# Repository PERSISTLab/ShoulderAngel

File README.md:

# Shoulder Angel: An Open Platform for Reprogramming Wayward Wireless Sensors

Software bugs are a critical threat to the deployability and maintainability of low-power wireless sensors, resulting in excess power consumption, hardware misconfigurations, incorrect data, and shortened device lifetimes. Worse, these errors can prevent wireless reprogramming, resulting in longer delays and costly human interventions. This repository contains the  Shoulder Angel—an ultra-low-power, low-cost, open hardware and software platform that ensures users can always recover and reprogram wireless sensors, in spite of software errors. Shoulder Angel uses a physically separate coprocessor to monitor a device’s power consumption and other behaviors, while keeping the device in a reprogrammable state. Our results show that Shoulder Angel is able to recover from otherwise fatal software errors while incurring an energy overhead of only 7 μW.

### Getting Started
Coming soon....

### License

```
Copyright (c) 2016 PERSIST Lab

Permission is hereby granted, free of charge, to any person obtaining a copy of this software 
and associated documentation files (the "Software"), to deal in the Software without restriction, 
including without limitation the rights to use, copy, modify, merge, publish, distribute, sublicense,
and/or sell copies of the Software, and to permit persons to whom the Software is furnished to do 
so, subject to the following conditions:

The above copyright notice and this permission notice shall be included in all copies or substantial
portions of the Software.

THE SOFTWARE IS PROVIDED "AS IS", WITHOUT WARRANTY OF ANY KIND, EXPRESS OR IMPLIED, 
INCLUDING BUT NOT LIMITED TO THE WARRANTIES OF MERCHANTABILITY, FITNESS FOR A PARTICULAR
PURPOSE AND NONINFRINGEMENT. IN NO EVENT SHALL THE AUTHORS OR COPYRIGHT HOLDERS BE LIABLE
FOR ANY CLAIM, DAMAGES OR OTHER LIABILITY, WHETHER IN AN ACTION OF CONTRACT, TORT OR 
OTHERWISE, ARISING FROM, OUT OF OR IN CONNECTION WITH THE SOFTWARE OR THE USE OR OTHER 
DEALINGS IN THE SOFTWARE.
```

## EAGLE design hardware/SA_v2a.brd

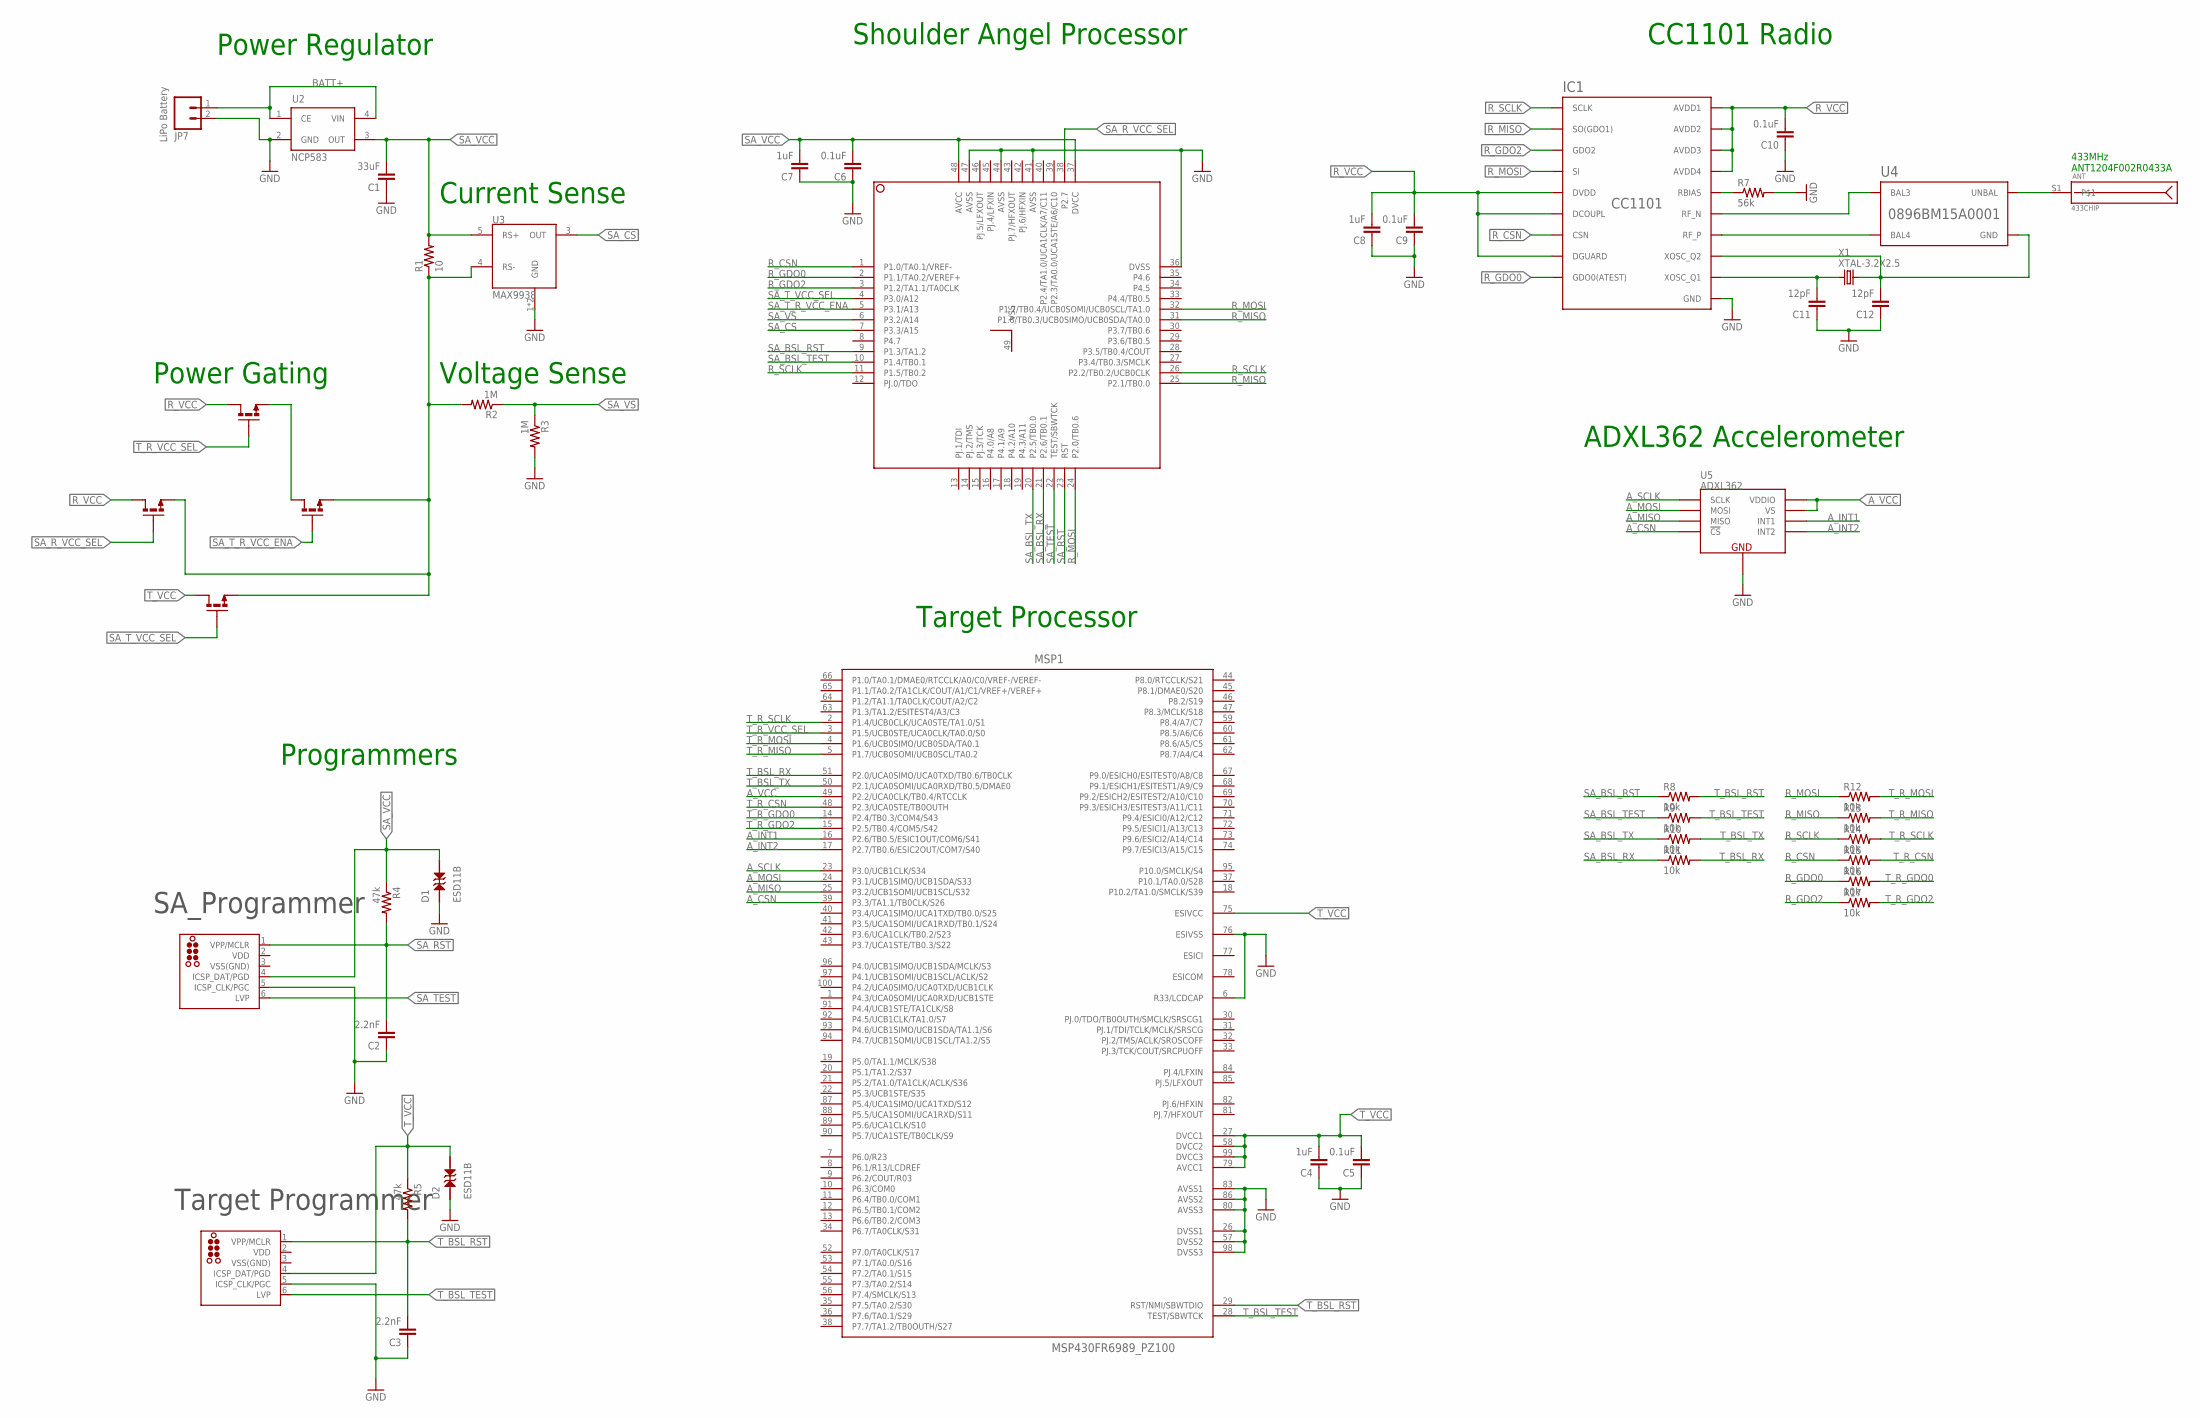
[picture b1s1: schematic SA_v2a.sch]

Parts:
ANT: 433CHIP; ANT-433-USP; DIGIKEY ANT-433-USP-ND
C1: 33uF; 0805; DIGIKEY 445-5986-1-ND
C2, C3: 2.2nF; 0402; DIGIKEY 311-1037-1-ND
C4, C7, C8: 1uF; 0402; DIGIKEY 311-1439-1-ND
C5, C6, C9, C10: 0.1uF; 0402; DIGIKEY 311-1338-1-ND
C11, C12: 12pF; 0402; DIGIKEY 1276-1178-1-ND
D1, D2: ESD11B; DSN2; DIGIKEY ESD11B5.0ST5GOSCT-ND
IC1: CC1101; QLP20; DIGIKEY 296-35718-1-ND
J1, J2: TC2030-MCP-NL
JP7: LiPo Battery; JST-2-SMD; DIGIKEY 455-1749-1-ND
MSP1: MSP430FR6989_PZ100; PZ100; DIGIKEY 296-38379-5-ND
R1: 10; 0402; DIGIKEY YAG3340CT-ND
R2, R3: 1M; 0402; DIGIKEY 311-1.00MLRCT-ND
R4, R5: 47k; 0402; DIGIKEY 311-47.0KLRCT-ND
R7: 56k; 0402; DIGIKEY 311-56KJRCT-ND
R8, R9, R10, R11, R12, R13, R14, R15, R16, R17: 10k; 0402; DIGIKEY 311-10KJRCT-ND
U1: MSP430FR5969_RGZ_48; RGZ48_4P1X4P1; DIGIKEY 296-37875-1-ND
U2: NCP583; SC82-AB_1PRIMARY; DIGIKEY NCP583SQ33T1GOSCT-ND
U3: MAX9938; SOT23-5; DIGIKEY MAX9938WEUK+TCT-ND
U4: 0896BM15A0001; XXXXBM15A0001; DIGIKEY 712-1474-1-ND
U5: ADXL362; DIGIKEY ADXL362BCCZ-RL7CT-ND
U$1, U$2: FDG6303N; SC70-6; DIGIKEY FDG6303NCT-ND
X1: XTAL-3.2X2.5; DIGIKEY 644-1261-1-ND

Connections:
A_CSN: MSP1.39 (P3.3/TA1.1/TB0CLK/S26), U5.P$8 (!CS)
A_INT1: MSP1.16 (P2.6/TB0.5/ESIC1OUT/COM6/S41), U5.P$11 (INT1)
A_INT2: MSP1.17 (P2.7/TB0.6/ESIC2OUT/COM7/S40), U5.P$9 (INT2)
A_MISO: MSP1.25 (P3.2/UCB1SOMI/UCB1SCL/S32), U5.P$7 (MISO)
A_MOSI: MSP1.24 (P3.1/UCB1SIMO/UCB1SDA/S33), U5.P$6 (MOSI)
A_SCLK: MSP1.23 (P3.0/UCB1CLK/S34), U5.P$4 (SCLK)
A_VCC: MSP1.49 (P2.2/UCA0CLK/TB0.4/RTCCLK), U5.P$1 (VDDIO), U5.P$14 (VS)
BATT+: JP7.1, U2.1 (CE), U2.4 (VIN)
GND: C1.1, C2.1, C3.1, C4.1, C5.1, C6.1, C7.1, C8.1, C9.1, C10.1, C11.1, C12.1, D1.P$1 (1), D2.P$1 (1), IC1.16 (GND), IC1.19 (GND), IC1.GND, IC1.GND1 (GND), IC1.GND2 (GND), IC1.GND3 (GND), IC1.GND4 (GND), IC1.GND5 (GND), J1.5 (ICSP_CLK/PGC), J2.5 (ICSP_CLK/PGC), JP7.2, MSP1.6 (R33/LCDCAP), MSP1.26 (DVSS1), MSP1.57 (DVSS2), MSP1.76 (ESIVSS), MSP1.80 (AVSS3), MSP1.83 (AVSS1), MSP1.86 (AVSS2), MSP1.98 (DVSS3), R3.2, R7.2, U1.36 (DVSS), U1.41 (AVSS), U1.44 (AVSS), U1.47 (AVSS), U2.2 (GND), U3.1 (GND), U3.2 (GND), U5.P$12 (GND), U5.P$13 (GND), U5.P$16 (GND)
unnamed: IC1.17 (RBIAS), R7.1
unnamed: IC1.12 (RF_P), U4.4 (BAL4)
unnamed: R1.1, R2.2, U3.4 (RS-), U$1.4 (S1), U$2.1 (S2), U$2.4 (S1)
unnamed: U$1.1 (S2), U$1.3 (D1)
unnamed: IC1.13 (RF_N), U4.3 (BAL3)
unnamed: C12.2, IC1.10 (XOSC_Q2), U4.2 (GND), U4.5 (GND), U4.6 (GND), X1.3 (2)
unnamed: C11.2, IC1.8 (XOSC_Q1), X1.1
unnamed: ANT.S1, U4.1 (UNBAL)
R_CSN: IC1.7 (CSN), R15.1, U1.1 (P1.0/TA0.1/VREF-)
R_GDO0: IC1.6 (GDO0(ATEST)), R16.1, U1.2 (P1.1/TA0.2/VEREF+)
R_GDO2: IC1.3 (GDO2), R17.1, U1.3 (P1.2/TA1.1/TA0CLK)
R_MISO: IC1.2 (SO(GDO1)), R13.1, U1.25 (P2.1/TB0.0), U1.31 (P1.6/TB0.3/UCB0SIMO/UCB0SDA/TA0.0)
R_MOSI: IC1.20 (SI), R12.1, U1.24 (P2.0/TB0.6), U1.32 (P1.7/TB0.4/UCB0SOMI/UCB0SCL/TA1.0)
R_SCLK: IC1.1 (SCLK), R14.1, U1.11 (P1.5/TB0.2), U1.26 (P2.2/TB0.2/UCB0CLK)
R_VCC: C8.2, C9.2, C10.2, IC1.4 (DVDD), IC1.5 (DCOUPL), IC1.9 (AVDD1), IC1.11 (AVDD2), IC1.14 (AVDD3), IC1.15 (AVDD4), IC1.18 (DGUARD), U$1.6 (D2), U$2.6 (D2)
SA_BSL_RST: R8.1, U1.9 (P1.3/TA1.2)
SA_BSL_RX: R11.1, U1.21 (P2.6/TB0.1)
SA_BSL_TEST: R9.1, U1.10 (P1.4/TB0.1)
SA_BSL_TX: R10.1, U1.20 (P2.5/TB0.0)
SA_CS: U1.7 (P3.3/A15), U3.3 (OUT)
SA_RST: C2.2, J1.1 (VPP/MCLR), R4.2, U1.23 (RST)
SA_R_VCC_SEL: U1.38 (P2.7), U$2.2 (G2)
SA_TEST: J1.6 (LVP), U1.22 (TEST/SBWTCK)
SA_T_R_VCC_ENA: U1.5 (P3.1/A13), U$1.5 (G1)
SA_T_VCC_SEL: U1.4 (P3.0/A12), U$2.5 (G1)
SA_VCC: C1.2, C6.2, C7.2, D1.P$2 (2), J1.4 (ICSP_DAT/PGD), R1.2, R4.1, U1.37 (DVCC), U1.48 (AVCC), U2.3 (OUT), U3.5 (RS+)
SA_VS: R2.1, R3.1, U1.6 (P3.2/A14)
T_BSL_RST: C3.2, J2.1 (VPP/MCLR), MSP1.29 (RST/NMI/SBWTDIO), R5.2, R8.2
T_BSL_RX: MSP1.51 (P2.0/UCA0SIMO/UCA0TXD/TB0.6/TB0CLK), R11.2
T_BSL_TEST: J2.6 (LVP), MSP1.28 (TEST/SBWTCK), R9.2
T_BSL_TX: MSP1.50 (P2.1/UCA0SOMI/UCA0RXD/TB0.5/DMAE0), R10.2
T_R_CSN: MSP1.48 (P2.3/UCA0STE/TB0OUTH), R15.2
T_R_GDO0: MSP1.14 (P2.4/TB0.3/COM4/S43), R16.2
T_R_GDO2: MSP1.15 (P2.5/TB0.4/COM5/S42), R17.2
T_R_MISO: MSP1.5 (P1.7/UCB0SOMI/UCB0SCL/TA0.2), R13.2
T_R_MOSI: MSP1.4 (P1.6/UCB0SIMO/UCB0SDA/TA0.1), R12.2
T_R_SCLK: MSP1.2 (P1.4/UCB0CLK/UCA0STE/TA1.0/S1), R14.2
T_R_VCC_SEL: MSP1.3 (P1.5/UCB0STE/UCA0CLK/TA0.0/S0), U$1.2 (G2)
T_VCC: C4.2, C5.2, D2.P$2 (2), J2.4 (ICSP_DAT/PGD), MSP1.27 (DVCC1), MSP1.58 (DVCC2), MSP1.75 (ESIVCC), MSP1.79 (AVCC1), MSP1.99 (DVCC3), R5.1, U$2.3 (D1)
VDD: J1.2 (VDD), J2.2 (VDD)
VSS(GND): J1.3 (VSS(GND)), J2.3 (VSS(GND))

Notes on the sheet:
433MHz ANT1204F002R0433A
Power Regulator
Current Sense
Voltage Sense
Power Gating
Shoulder Angel Processor
CC1101 Radio
ADXL362 Accelerometer
Target Processor
Programmers
SA_Programmer
Target Programmer

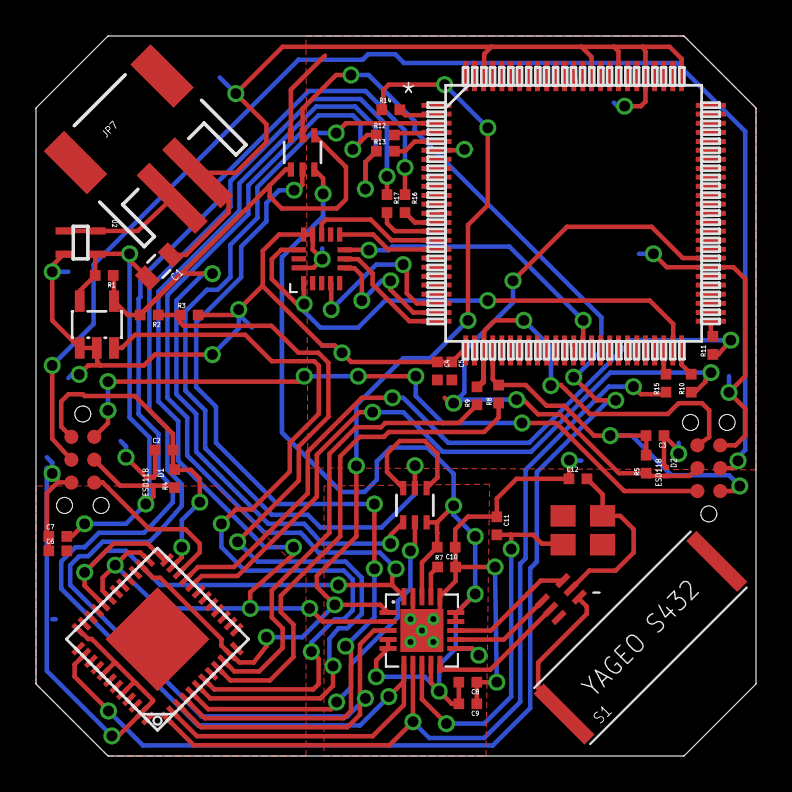
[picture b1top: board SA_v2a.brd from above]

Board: 2 copper layers, 40.0 x 40.0 mm, 44 parts (0 on the bottom side), 50 nets.

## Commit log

2016-09-17 Update LICENSE
2017-01-04 Adding relevant files to this repo

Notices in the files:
parts and their libraries:
tag-connect_msp430: ©2009 ROFA.cz - modified and updated by Robert Darlington ‹rdarlington@gmail.com›
SparkFun-Capacitors: Licensing: Creative Commons ShareAlike 4.0 International - https://creativecommons.org/licenses/by-sa/4.0
